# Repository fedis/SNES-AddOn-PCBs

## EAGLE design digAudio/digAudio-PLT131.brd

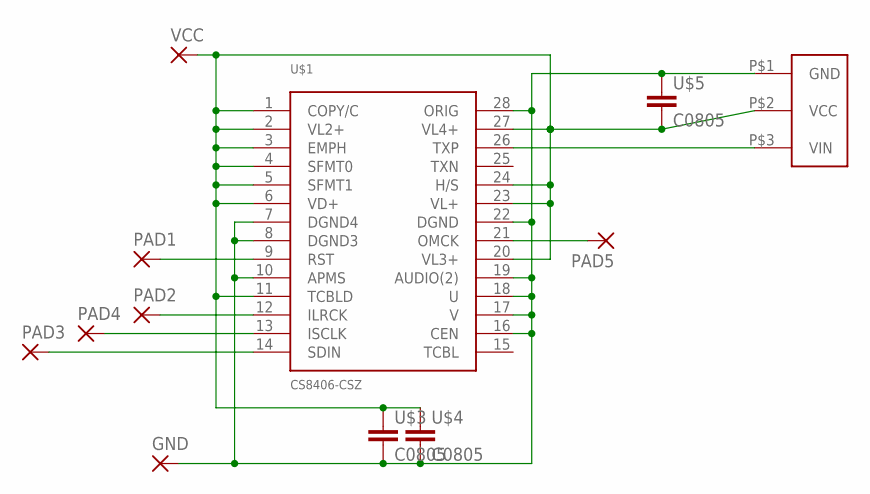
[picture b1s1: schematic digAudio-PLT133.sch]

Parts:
GND: SMD2; SMD1,27-2,54
PAD1, PAD2, PAD3, PAD4, PAD5: SMD2; SMD1,27-2,54
U$1: CS8406-CSZ; SO28W
U$3, U$4, U$5: C0805; Z0805
U$6: PLT133/T10W
VCC: SMD2; SMD1,27-2,54

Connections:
GND: GND.1, U$1.7 (DGND4), U$1.8 (DGND3), U$1.10 (APMS), U$1.16 (CEN), U$1.17 (V), U$1.18 (U), U$1.19 (AUDIO(2)), U$1.22 (DGND), U$1.28 (ORIG), U$3.2, U$4.2, U$5.1, U$6.P$1 (GND); also elsewhere on the board
unnamed 1: U$1.26 (TXP), U$6.P$3 (VIN); also elsewhere on the board
unnamed: PAD1.1, U$1.9 (RST)
unnamed: PAD2.1, U$1.12 (ILRCK)
unnamed: PAD4.1, U$1.13 (ISCLK)
unnamed: PAD3.1, U$1.14 (SDIN)
unnamed: PAD5.1, U$1.21 (OMCK)
VCC: U$1.1 (COPY/C), U$1.2 (VL2+), U$1.3 (EMPH), U$1.4 (SFMT0), U$1.5 (SFMT1), U$1.6 (VD+), U$1.11 (TCBLD), U$1.20 (VL3+), U$1.23 (VL+), U$1.24 (H/S), U$1.27 (VL4+), U$3.1, U$4.1, U$5.2, U$6.P$2 (VCC), VCC.1; also elsewhere on the board

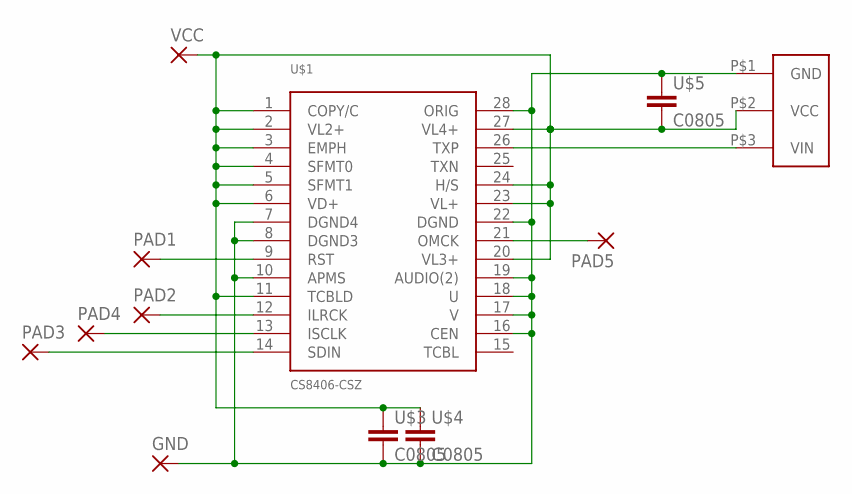
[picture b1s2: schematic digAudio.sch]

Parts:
GND: SMD2; SMD1,27-2,54
PAD1, PAD2, PAD3, PAD4, PAD5: SMD2; SMD1,27-2,54
U$1: CS8406-CSZ; SO28W
U$2: PHOTOLINK; PHOTOLONK
U$3, U$4, U$5: C0805; Z0805
VCC: SMD2; SMD1,27-2,54

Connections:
GND: GND.1, U$1.7 (DGND4), U$1.8 (DGND3), U$1.10 (APMS), U$1.16 (CEN), U$1.17 (V), U$1.18 (U), U$1.19 (AUDIO(2)), U$1.22 (DGND), U$1.28 (ORIG), U$2.P$1 (GND), U$3.2, U$4.2, U$5.1; also elsewhere on the board
unnamed 1: U$1.26 (TXP), U$2.P$3 (VIN); also elsewhere on the board
unnamed: PAD1.1, U$1.9 (RST)
unnamed: PAD2.1, U$1.12 (ILRCK)
unnamed: PAD4.1, U$1.13 (ISCLK)
unnamed: PAD3.1, U$1.14 (SDIN)
unnamed: PAD5.1, U$1.21 (OMCK)
VCC: U$1.1 (COPY/C), U$1.2 (VL2+), U$1.3 (EMPH), U$1.4 (SFMT0), U$1.5 (SFMT1), U$1.6 (VD+), U$1.11 (TCBLD), U$1.20 (VL3+), U$1.23 (VL+), U$1.24 (H/S), U$1.27 (VL4+), U$2.P$2 (VCC), U$3.1, U$4.1, U$5.2, VCC.1; also elsewhere on the board

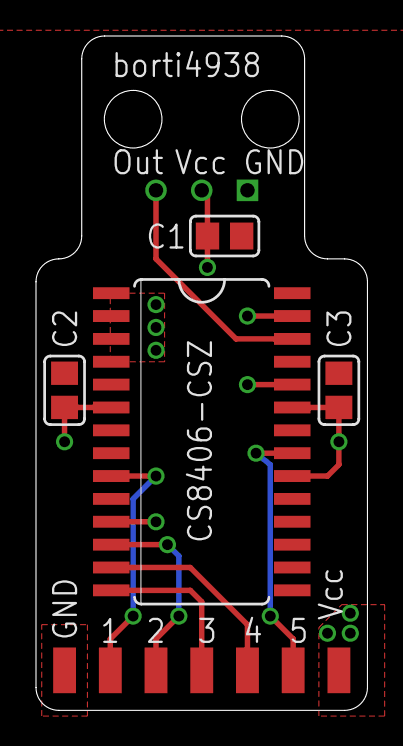
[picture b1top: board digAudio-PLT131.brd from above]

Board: 2 copper layers, 18.4 x 37.5 mm, 12 parts (0 on the bottom side), 8 nets.
